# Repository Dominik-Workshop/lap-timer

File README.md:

# Lap Timer

## Overview

Compact and portable **lap timer**, capable of measuring time on:

- **Closed-loop tracks** (1-gate mode)
- **Start/finish tracks** (2-gate mode)

Infrared light barriers are used as optical triggers to detect when an object crosses the start or finish line.

### Key Features

- **High accuracy** using STM32 hardware timers
- **OLED display** for showing lap times
- **Two operating modes:** 1-gate or 2-gate
- **Modulated IR system (38 kHz)** for ambient light immunity

## Project Status

**Design:** ✅ --> **Fabrication & Assembly:** ✅ --> **Bring-up:** ✅

## Electronics

Simplified arhitecture of the **Lap Timer** is shown on the block diagram bellow:

This project contains 3 custom PCBs:

- [**Timer board**](/pcb/timer-board/): main PCB of the system, responsible for time measurement and displaying results

<!--  -->

- [**Transmitter board**](/pcb/transmitter-board/): generates the modulated IR light beam for the optical barrier

<!--  -->

- [**Receiver board**](/pcb/receiver-board/): (used only in 2-gate mode) detects the IR signal and triggers the timer

<!--  -->

## Mechanical

Each board has a custom-designed **3D printed enclosure**.

## Used Tools

- [KiCad](https://www.kicad.org/) - Schematic and PCB design
- [Autodesk Fusion 360](https://www.autodesk.com/products/fusion-360/) - 3D modeling
- [STM32CubeIDE](https://www.st.com/en/development-tools/stm32cubeide.html) - STM32 firmware development (build/flash/debug)

## Authors

- [**Dominik Pluta**](https://github.com/Dominik-Workshop):
  - **Responsibility**: [**Timer board**](/pcb/timer-board/)
- [**Mateusz Gwioździk**](https://github.com/Nojilim):
  - **Responsibility**: [**Transmitter board**](/pcb/transmitter-board/)
- [**Radek Mierzwa**](https://github.com/Radek278):
  - **Responsibility**: [**Receiver board**](/pcb/receiver-board/)

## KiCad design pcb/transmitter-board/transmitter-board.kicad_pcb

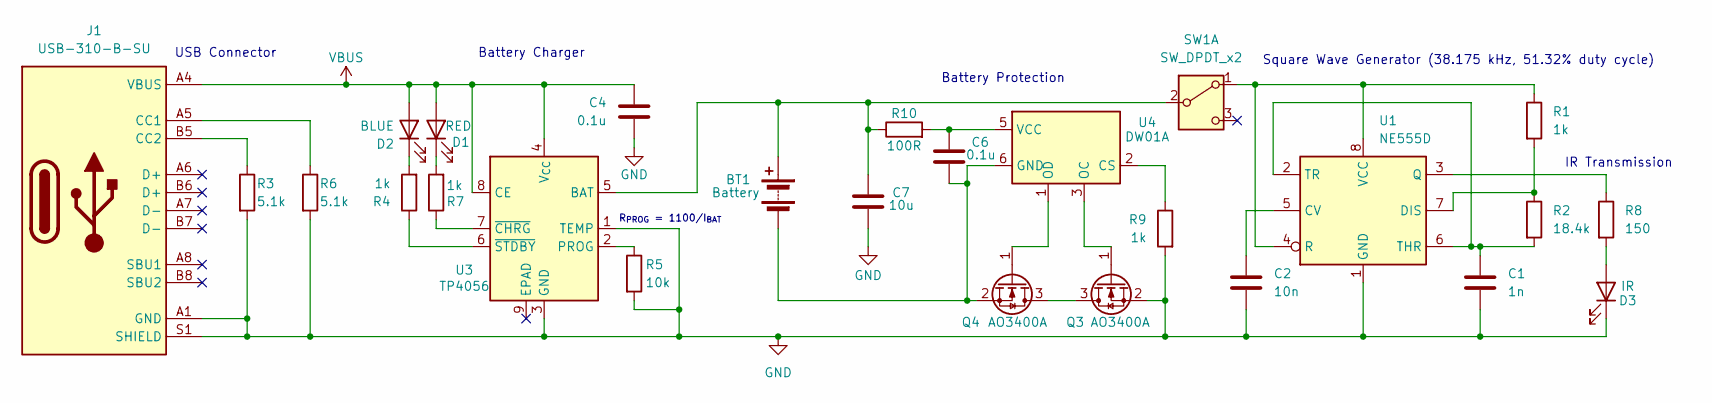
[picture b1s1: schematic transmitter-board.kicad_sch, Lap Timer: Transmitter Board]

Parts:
BT1: Battery; PinSocket_1x02_P2.54mm_Vertical
C1: 1n; C_0603_1608Metric_Pad1.08x0.95mm_HandSolder
C2: 10n; C_0603_1608Metric_Pad1.08x0.95mm_HandSolder
C4, C6: 0.1u; C_0603_1608Metric_Pad1.08x0.95mm_HandSolder
C7: 10u; C_0603_1608Metric_Pad1.08x0.95mm_HandSolder
D1: RED; LED_0603_1608Metric_Pad1.05x0.95mm_HandSolder
D2: BLUE; LED_0603_1608Metric_Pad1.05x0.95mm_HandSolder
D3: IR; LED_THT_Horizontal_SMD_mounted
J1: USB-C_USB-310F-B-SU; USB-C-Receptacle_USB-310-B-SU; MPN USB-310-B-SU; LCSC C309347
Q3, Q4: AO3400A; SOT-23
R1, R4, R7, R9: 1k; R_0603_1608Metric_Pad0.98x0.95mm_HandSolder
R2: 18.4k; R_0603_1608Metric_Pad0.98x0.95mm_HandSolder
R3, R6: 5.1k; R_0603_1608Metric_Pad0.98x0.95mm_HandSolder
R5: 10k; R_0603_1608Metric_Pad0.98x0.95mm_HandSolder
R8: 150; R_0603_1608Metric_Pad0.98x0.95mm_HandSolder
R10: 100R; R_0603_1608Metric_Pad0.98x0.95mm_HandSolder
SW1: SW_DPDT_x2; SW_DPDT_CK_JS202011JCQN
U1: NE555D; SOIC-8_3.9x4.9mm_P1.27mm
U3: TP4056; SOIC-8-1EP_3.9x4.9mm_P1.27mm_EP2.41x3.3mm_ThermalVias
U4: DW01A; SOT-23-6

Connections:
GND: C1.2, C2.2, C4.2, C7.2, D3.1 (K), J1.A1 (GND), J1.A12 (GND), J1.B1 (GND), J1.B12 (GND), J1.S1 (SHIELD), Q3.2 (S), R3.2, R5.2, R6.2, R9.2, U1.1 (GND), U3.1 (TEMP), U3.3 (GND)
unnamed: BT1.1 (+), C7.1, R10.1, SW1.2 (B), U3.5 (BAT)
unnamed: BT1.2 (-), C6.2, Q4.2 (S), U4.6 (GND)
unnamed: D1.1 (K), R7.2
unnamed: D2.1 (K), R4.2
unnamed: D3.2 (A), R8.2
unnamed: J1.A5 (CC1), R6.1
unnamed: J1.B5 (CC2), R3.1
unnamed: Q3.3 (D), Q4.3 (D)
unnamed: Q3.1 (G), U4.3 (OC)
unnamed: Q4.1 (G), U4.1 (OD)
unnamed: R1.1, SW1.1 (A), U1.4 (R), U1.8 (VCC)
unnamed: C2.1, U1.5 (CV)
unnamed: R1.2, R2.1, U1.7 (DIS)
unnamed: R8.1, U1.3 (Q)
unnamed: C1.1, R2.2, U1.2 (TR), U1.6 (THR)
unnamed: R5.1, U3.2 (PROG)
unnamed: R7.1, U3.7 (~CHRG)
unnamed: R4.1, U3.6 (~STDBY)
unnamed: R9.1, U4.2 (CS)
unnamed: C6.1, R10.2, U4.5 (VCC)
VBUS: C4.1, D1.2 (A), D2.2 (A), J1.A4 (VBUS), J1.A9 (VBUS), J1.B4 (VBUS), J1.B9 (VBUS), U3.4 (V_{CC}), U3.8 (CE)

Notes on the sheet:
IR Transmission
R_{PROG} = 1100/I_{BAT}
Battery Protection
USB Connector
Battery Charger
Square Wave Generator (38.175 kHz, 51.32% duty cycle)

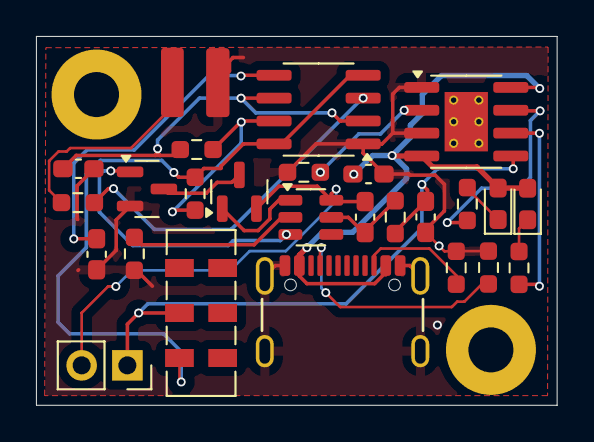
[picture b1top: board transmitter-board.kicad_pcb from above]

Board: 2 copper layers, 28.9 x 20.5 mm, 26 parts (0 on the bottom side), 22 nets.

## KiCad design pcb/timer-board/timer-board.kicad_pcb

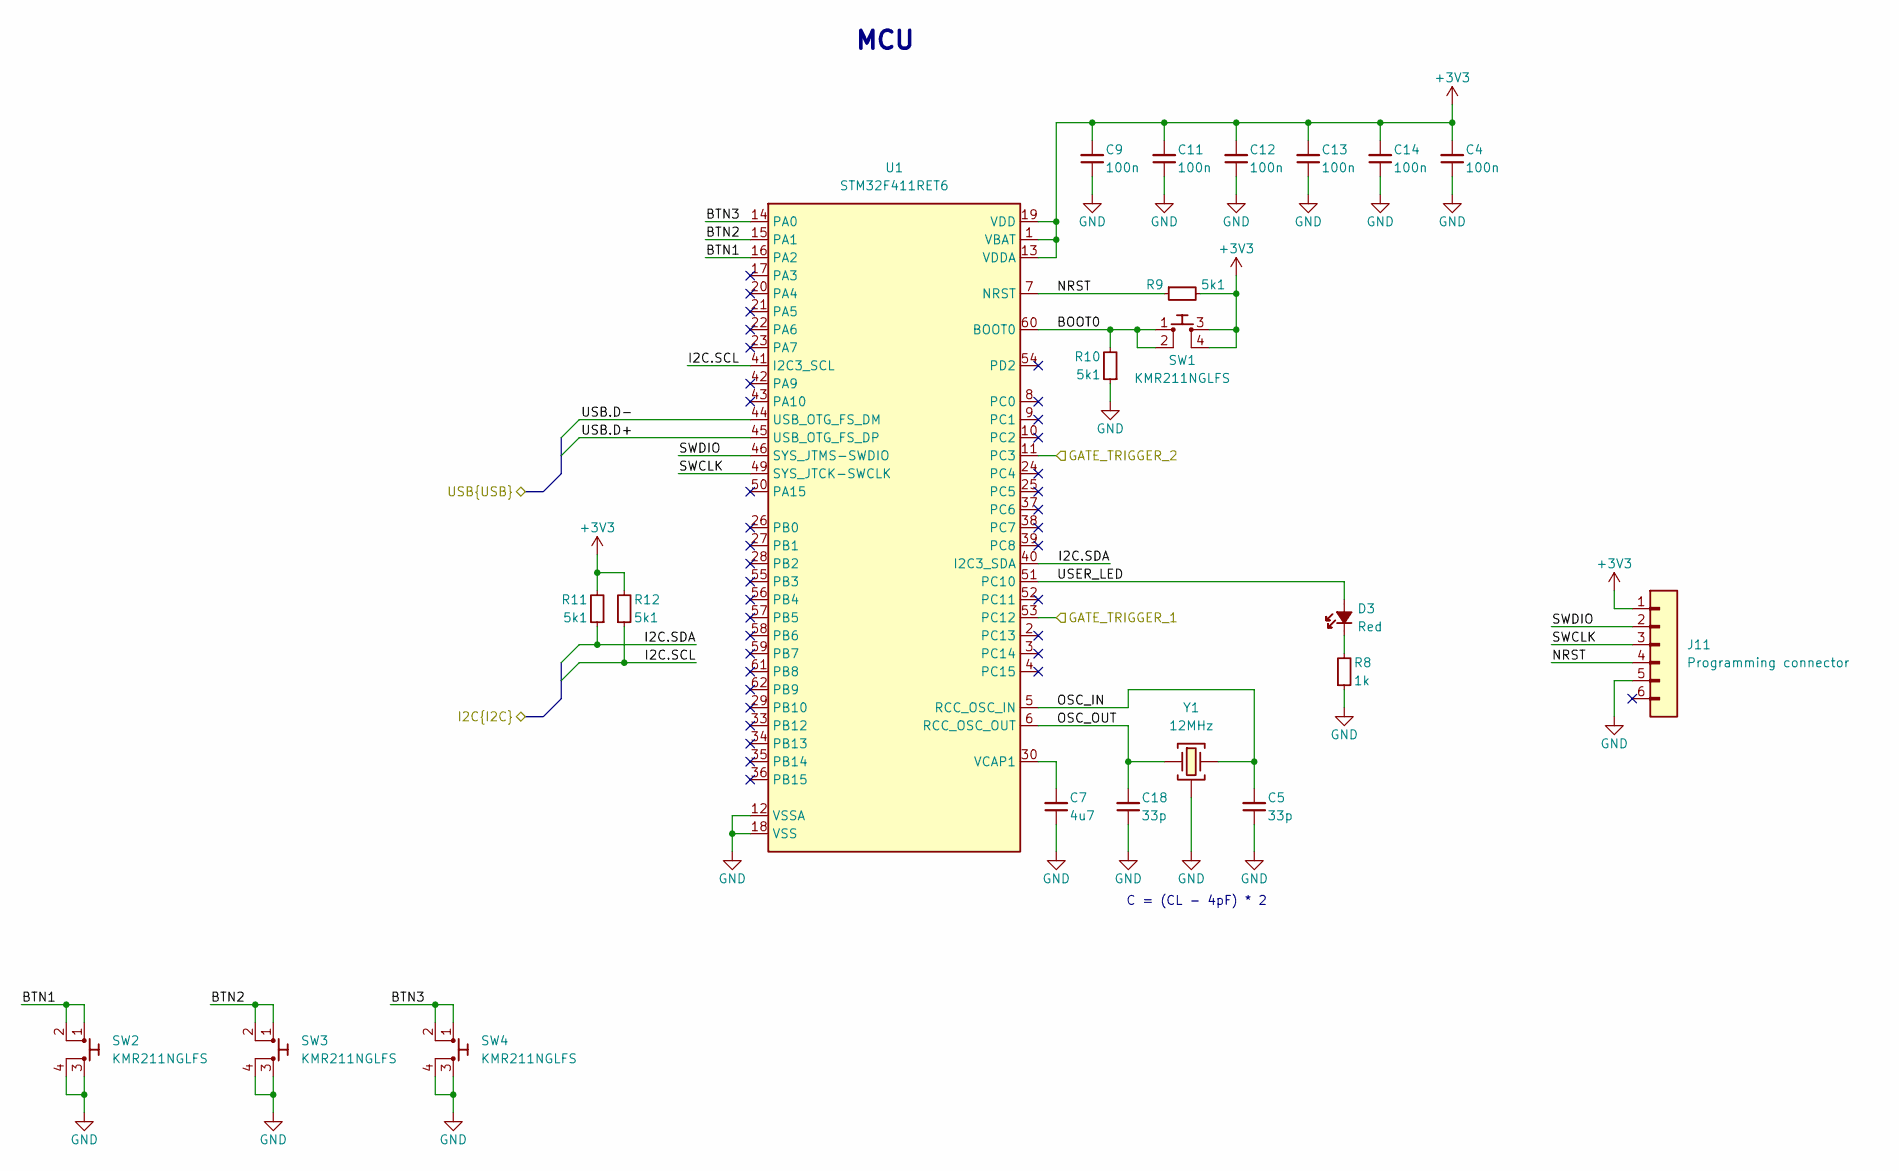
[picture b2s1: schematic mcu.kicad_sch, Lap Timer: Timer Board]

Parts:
C4, C9, C11, C12, C13, C14: C-100n-0402; C_0402_1005Metric; Tolerance 10%; Voltage 50V; MPN CL05B104KB54PNC; LCSC C307331
C5, C18: C-33p-0402; C_0402_1005Metric; Tolerance 5%; Voltage 50V; MPN 0402CG330J500NT; LCSC C1562
C7: C-4u7-0402; C_0402_1005Metric; Tolerance 20%; Voltage 10V; MPN CL05A475MP5NRNC; LCSC C23733
D3: LED-R-0603_KT-0603R; LED_0603_1608Metric_R; Forward voltage 1.8V-2.4V; MPN KT-0603R; LCSC C2286
J11: Programming connector; Custom-programming-connector-1x6_P1.27mm
R8: R-1k-0402; R_0402_1005Metric; Tolerance 1%; MPN 0402WGF1001TCE; LCSC C11702
R9, R10, R11, R12: R-5k1-0402; R_0402_1005Metric; Tolerance 1%; MPN 0402WGF5101TCE; LCSC C25905
SW1, SW2, SW3, SW4: SW_KMR211NGLFS; MPN KMR211NGLFS; LCSC C221676
U1: STM32F411RET6; LQFP-64_10x10mm_P0.5mm; MPN STM32F411RET6; LCSC C94355
Y1: X322512MSB4SI; Crystal_SMD_3225-4Pin_3.2x2.5mm; Frequency Tolerance ±10ppm; MPN X322512MSB4SI; LCSC C9002

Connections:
+3V3: C4.2, C9.2, C11.2, C12.2, C13.2, C14.2, J11.1, R9.2, R11.2, R12.2, SW1.3, SW1.4, U1.1 (VBAT), U1.13 (VDDA), U1.19 (VDD), U1.32 (VDD), U1.48 (VDD), U1.64 (VDD); also elsewhere on the board
/Display/I2C.SCL: R12.1, U1.41 (I2C3_SCL); also elsewhere on the board
/Display/I2C.SDA: R11.1, U1.40 (I2C3_SDA); also elsewhere on the board
/IR receiver/GATE_TRIGGER_1: U1.53 (PC12); also elsewhere on the board
/IR receiver/GATE_TRIGGER_2: U1.11 (PC3); also elsewhere on the board
/MCU/BOOT0: R10.2, SW1.1, SW1.2, U1.60 (BOOT0)
/MCU/BTN1: SW2.1, SW2.2, U1.16 (PA2)
/MCU/BTN2: SW3.1, SW3.2, U1.15 (PA1)
/MCU/BTN3: SW4.1, SW4.2, U1.14 (PA0)
/MCU/NRST: J11.4, R9.1, U1.7 (NRST)
/MCU/OSC_IN: C5.2, U1.5 (RCC_OSC_IN), Y1.3
/MCU/OSC_OUT: C18.2, U1.6 (RCC_OSC_OUT), Y1.1
/MCU/SWCLK: J11.3, U1.49 (SYS_JTCK-SWCLK)
/MCU/SWDIO: J11.2, U1.46 (SYS_JTMS-SWDIO)
/MCU/USB.D+: U1.45 (USB_OTG_FS_DP); also elsewhere on the board
/MCU/USB.D-: U1.44 (USB_OTG_FS_DM); also elsewhere on the board
/MCU/USER_LED: D3.2 (A), U1.51 (PC10)
GND: C4.1, C5.1, C7.1, C9.1, C11.1, C12.1, C13.1, C14.1, C18.1, J11.5, R8.1, R10.1, SW2.3, SW2.4, SW3.3, SW3.4, SW4.3, SW4.4, U1.12 (VSSA), U1.18 (VSS), U1.31 (VSS), U1.47 (VSS), U1.63 (VSS), Y1.2 (SH), Y1.4 (SH); also elsewhere on the board
unnamed: D3.1 (C), R8.2
unnamed: C7.2, U1.30 (VCAP1)

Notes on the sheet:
C = (CL - 4pF) * 2
MCU

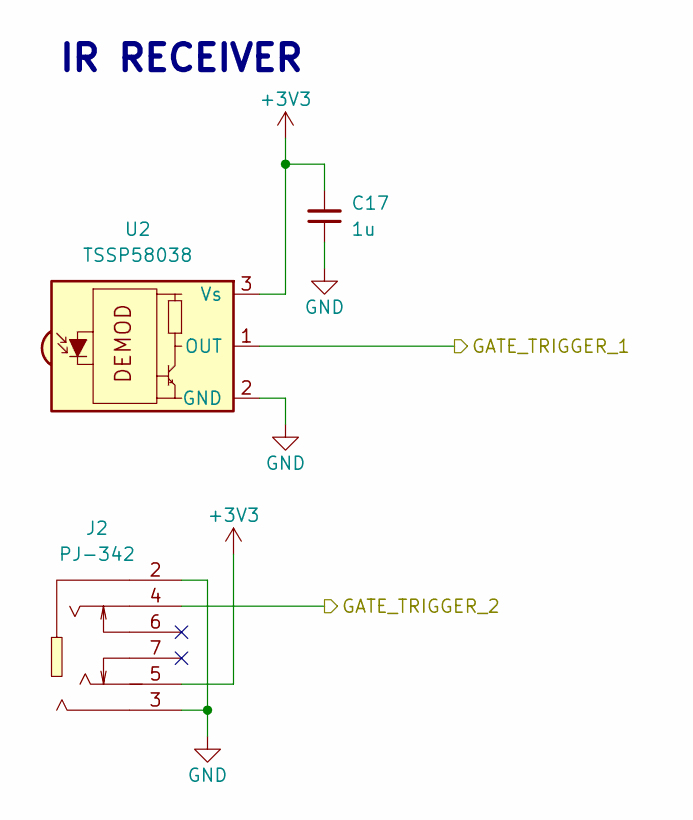
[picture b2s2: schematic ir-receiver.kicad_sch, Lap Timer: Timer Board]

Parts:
C17: C-1u-0402; C_0402_1005Metric; Tolerance 10%; Voltage 25V; MPN CL05A105KA5NQNC; LCSC C52923
J2: Jack_PJ-342; MPN PJ-342; LCSC C668606
U2: TSSP58038; Vishay_MINICAST-3Pin

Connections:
+3V3: C17.2, J2.5, U2.3 (Vs); also elsewhere on the board
/IR receiver/GATE_TRIGGER_1: U2.1 (OUT); also elsewhere on the board
/IR receiver/GATE_TRIGGER_2: J2.4; also elsewhere on the board
GND: C17.1, J2.2, J2.3, U2.2 (GND); also elsewhere on the board

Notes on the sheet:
IR RECEIVER

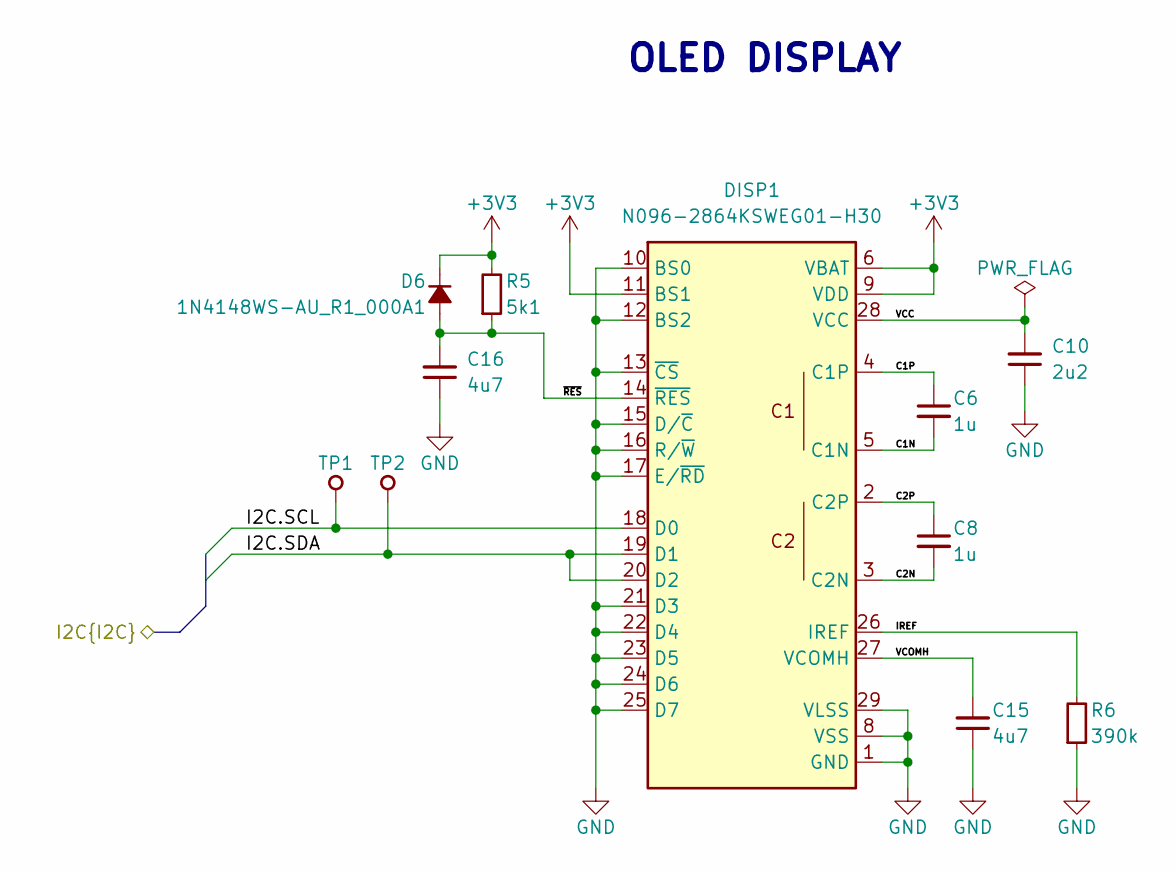
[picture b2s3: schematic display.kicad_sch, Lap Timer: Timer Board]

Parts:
C6, C8: C-1u-0402; C_0402_1005Metric; Tolerance 10%; Voltage 25V; MPN CL05A105KA5NQNC; LCSC C52923
C10: C-2u2-0402; C_0402_1005Metric; Tolerance 20%; Voltage 6.3V; MPN CL05A225MQ5NSNC; LCSC C12530
C15, C16: C-4u7-0402; C_0402_1005Metric; Tolerance 20%; Voltage 10V; MPN CL05A475MP5NRNC; LCSC C23733
D6: 1N4148WS-AU; D_SOD-323F; Reverse Voltage 75V; MPN 1N4148WS-AU_R1_000A1; LCSC C2999083
DISP1: N096-2864KSWEG01-H30; MPN N096-2864KSWEG01-H30
R5: R-5k1-0402; R_0402_1005Metric; Tolerance 1%; MPN 0402WGF5101TCE; LCSC C25905
R6: R-390k-0402; R_0402_1005Metric; Tolerance 1%; MPN 0402WGF3903TCE; LCSC C25782
TP1, TP2: TP_SMD_1mm

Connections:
+3V3: D6.1 (C), DISP1.6 (VBAT), DISP1.9 (VDD), DISP1.11 (BS1), R5.2; also elsewhere on the board
/Display/C1N: C6.2, DISP1.5 (C1N)
/Display/C1P: C6.1, DISP1.4 (C1P)
/Display/C2N: C8.2, DISP1.3 (C2N)
/Display/C2P: C8.1, DISP1.2 (C2P)
/Display/I2C.SCL: DISP1.18 (D0), TP1.1; also elsewhere on the board
/Display/I2C.SDA: DISP1.19 (D1), DISP1.20 (D2), TP2.1; also elsewhere on the board
/Display/IREF: DISP1.26 (IREF), R6.2
/Display/VCC: C10.2, DISP1.28 (VCC)
/Display/VCOMH: C15.2, DISP1.27 (VCOMH)
/Display/~RES: C16.2, D6.2 (A), DISP1.14 (~RES), R5.1
GND: C10.1, C15.1, C16.1, DISP1.1 (GND), DISP1.8 (VSS), DISP1.10 (BS0), DISP1.12 (BS2), DISP1.13 (~CS), DISP1.15 (D/~C), DISP1.16 (R/~W), DISP1.17 (E/~RD), DISP1.21 (D3), DISP1.22 (D4), DISP1.23 (D5), DISP1.24 (D6), DISP1.25 (D7), DISP1.29 (VLSS), DISP1.30 (GND), R6.1; also elsewhere on the board

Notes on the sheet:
OLED DISPLAY

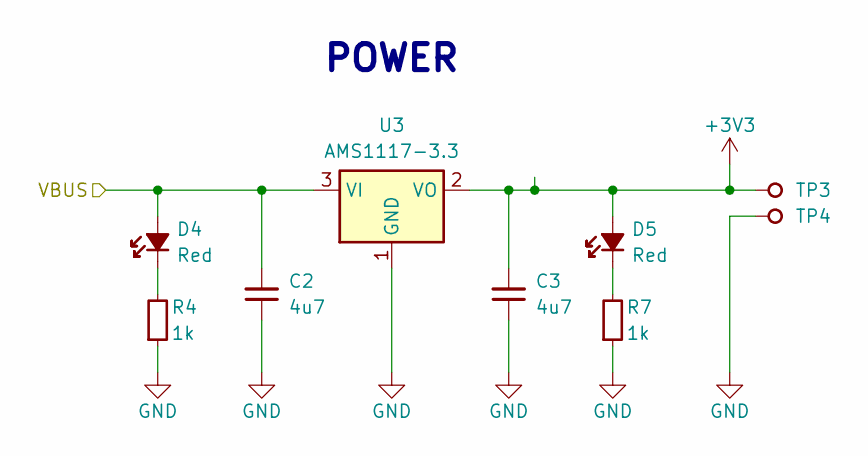
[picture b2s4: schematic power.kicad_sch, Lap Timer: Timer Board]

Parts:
C2, C3: C-4u7-0402; C_0402_1005Metric; Tolerance 20%; Voltage 10V; MPN CL05A475MP5NRNC; LCSC C23733
D4, D5: LED-R-0603_KT-0603R; LED_0603_1608Metric_R; Forward voltage 1.8V-2.4V; MPN KT-0603R; LCSC C2286
R4, R7: R-1k-0402; R_0402_1005Metric; Tolerance 1%; MPN 0402WGF1001TCE; LCSC C11702
TP3, TP4: TP_SMD_1mm
U3: AMS1117-3.3; SOT-223-3_TabPin2

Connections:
+3V3: C3.2, D5.2 (A), TP3.1, U3.2 (VO); also elsewhere on the board
/Power/VBUS: C2.2, D4.2 (A), U3.3 (VI); also elsewhere on the board
GND: C2.1, C3.1, R4.1, R7.1, TP4.1, U3.1 (GND); also elsewhere on the board
unnamed: D4.1 (C), R4.2
unnamed: D5.1 (C), R7.2

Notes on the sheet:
POWER

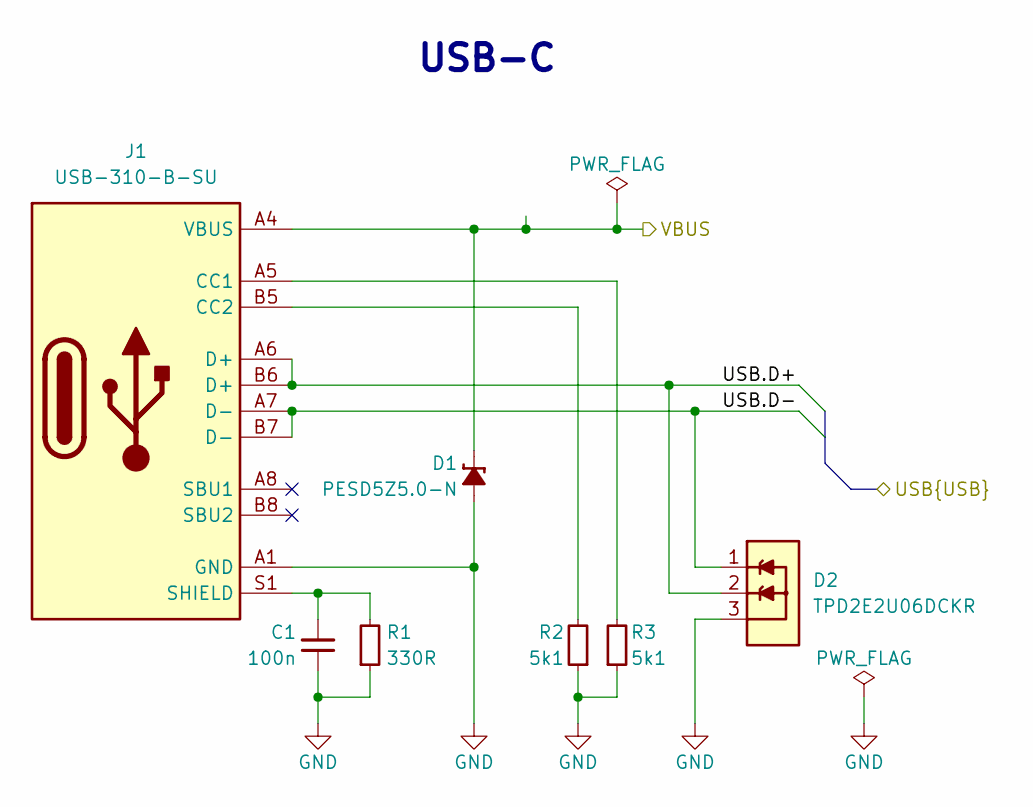
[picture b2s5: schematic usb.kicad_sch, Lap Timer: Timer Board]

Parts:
C1: C-100n-0402; C_0402_1005Metric; Tolerance 10%; Voltage 50V; MPN CL05B104KB54PNC; LCSC C307331
D1: PESD5Z5; D_SOD-523; MPN PESD5Z5.0-N; LCSC C920301
D2: TPD2E2U06DCKR; SOT-323; MPN TPD2E2U06DCKR; LCSC C1855726
J1: USB-C_USB-310F-B-SU; USB-C-Receptacle_USB-310-B-SU; MPN USB-310-B-SU; LCSC C309347
R1: R-330r-0402; R_0402_1005Metric; Tolerance 1%; MPN 0402WGF3300TCE; LCSC C25104
R2, R3: R-5k1-0402; R_0402_1005Metric; Tolerance 1%; MPN 0402WGF5101TCE; LCSC C25905

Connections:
/MCU/USB.D+: D2.2, J1.A6 (D+), J1.B6 (D+); also elsewhere on the board
/MCU/USB.D-: D2.1, J1.A7 (D-), J1.B7 (D-); also elsewhere on the board
/Power/VBUS: D1.1 (C), J1.A4 (VBUS), J1.A9 (VBUS), J1.B4 (VBUS), J1.B9 (VBUS); also elsewhere on the board
GND: C1.1, D1.2 (A), D2.3, J1.A1 (GND), J1.A12 (GND), J1.B1 (GND), J1.B12 (GND), R1.1, R2.1, R3.1; also elsewhere on the board
unnamed: J1.A5 (CC1), R3.2
unnamed: J1.B5 (CC2), R2.2
unnamed: C1.2, J1.S1 (SHIELD), R1.2

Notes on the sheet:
USB-C

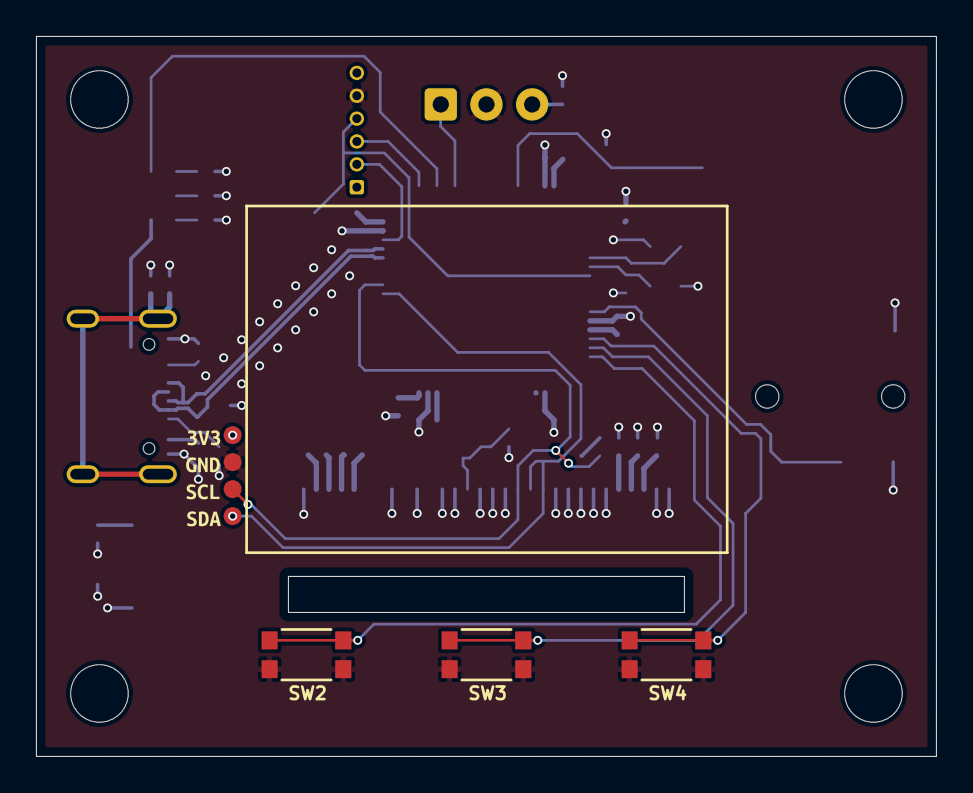
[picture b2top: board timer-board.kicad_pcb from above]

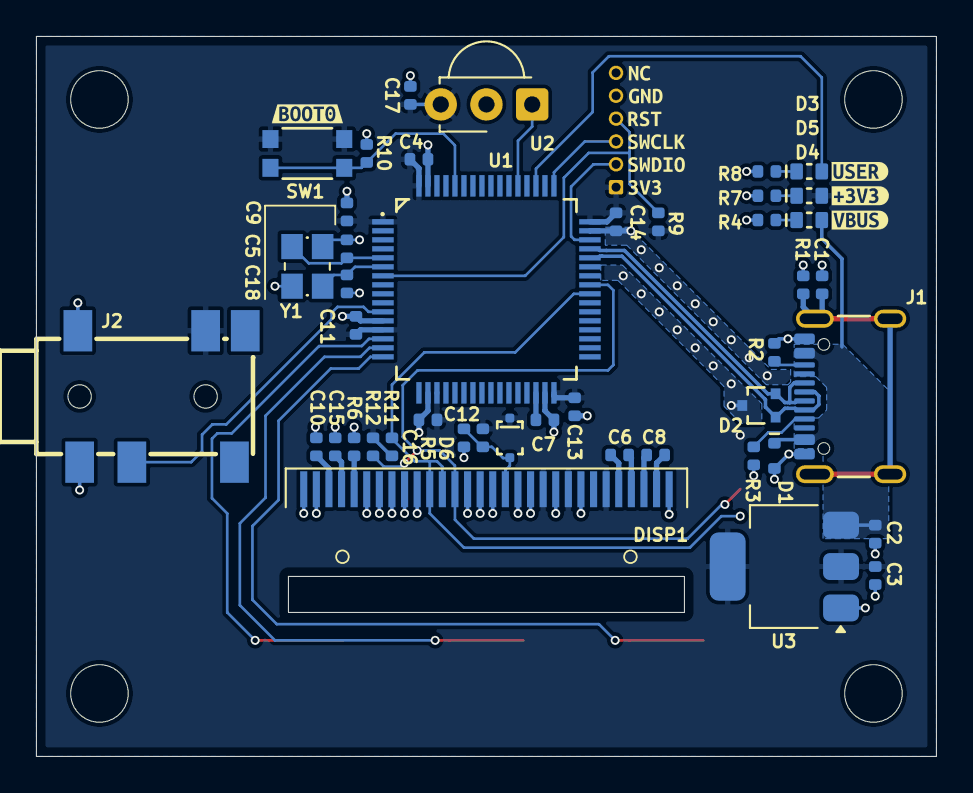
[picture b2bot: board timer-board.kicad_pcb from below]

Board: 2 copper layers, 50.0 x 40.0 mm, 66 parts (55 on the bottom side), 34 nets.

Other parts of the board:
kibuzzard-68E6B0E6: G***; kibuzzard-68E6B0E6
kibuzzard-68E6B17C: G***; kibuzzard-68E6B17C
kibuzzard-68E6B138: G***; kibuzzard-68E6B138
kibuzzard-68E6B152: G***; kibuzzard-68E6B152
kibuzzard-68E6B182: G***; kibuzzard-68E6B182
kibuzzard-68FD2D82: G***; kibuzzard-68FD2D82
kibuzzard-690B1D8E: G***; kibuzzard-690B1D8E
kibuzzard-690B1DCB: G***; kibuzzard-690B1DCB
kibuzzard-690B1DD3: G***; kibuzzard-690B1DD3
kibuzzard-690B1DD8: G***; kibuzzard-690B1DD8
kibuzzard-690B8D6F: G***; kibuzzard-690B8D6F
kibuzzard-691094F6: G***; kibuzzard-691094F6
kibuzzard-69109507: G***; kibuzzard-69109507
kibuzzard-69109536: G***; kibuzzard-69109536

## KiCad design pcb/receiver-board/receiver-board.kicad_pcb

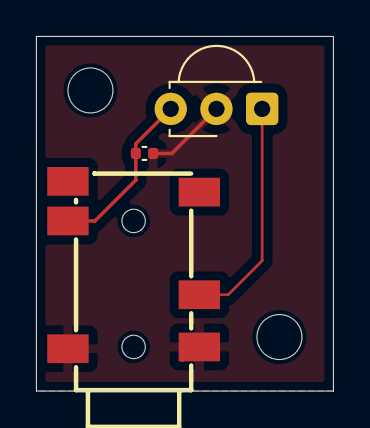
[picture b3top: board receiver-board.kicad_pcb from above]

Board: 2 copper layers, 16.5 x 19.7 mm, 3 parts (0 on the bottom side), 3 nets.

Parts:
C6: C-1u-0402; C_0402_1005Metric
J2: Jack_PJ-342
U2: TSSP58038; Vishay_MINICAST-3Pin

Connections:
+3V3: C6.1, J2.5, U2.3 (Vs)
/GATE_TRIGGER2: J2.4, U2.1 (OUT)
GND: C6.2, J2.2, J2.3, U2.2 (GND)

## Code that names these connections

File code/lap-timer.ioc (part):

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Mcu.Name=STM32F411R(C-E)Tx
Mcu.Package=LQFP64
Mcu.UserName=STM32F411RETx
PA0-WKUP.GPIOParameters=GPIO_PuPd,GPIO_Label
PA0-WKUP.GPIO_Label=BTN3
PA0-WKUP.GPIO_PuPd=GPIO_PULLUP
PA0-WKUP.Signal=GPIO_Input
PA1.GPIOParameters=GPIO_PuPd,GPIO_Label
PA1.GPIO_Label=BTN2
PA1.GPIO_PuPd=GPIO_PULLUP
PA1.Signal=GPIO_Input
PA2.GPIOParameters=GPIO_PuPd,GPIO_Label
PA2.GPIO_Label=BTN1
PA2.GPIO_PuPd=GPIO_PULLUP
PA2.Signal=GPXTI2
PA8.Mode=I2C
PA8.Signal=I2C3_SCL
PC10.GPIOParameters=GPIO_Label
PC10.GPIO_Label=USER_LED
PC10.Signal=GPIO_Output
PC12.GPIOParameters=GPIO_PuPd,GPIO_Label,GPIO_ModeDefaultEXTI
PC12.GPIO_Label=GATE_TRIGGER_1
PC12.GPIO_ModeDefaultEXTI=GPIO_MODE_IT_RISING
PC12.GPIO_PuPd=GPIO_PULLUP
PC12.Signal=GPXTI12
PC3.GPIOParameters=GPIO_PuPd,GPIO_Label
PC3.GPIO_Label=GATE_TRIGGER_2
PC3.GPIO_PuPd=GPIO_PULLUP
PC3.Signal=GPXTI3
PC9.Mode=I2C
PC9.Signal=I2C3_SDA
PH0\ -\ OSC_IN.Mode=HSE-External-Oscillator
PH0\ -\ OSC_IN.Signal=RCC_OSC_IN
PH1\ -\ OSC_OUT.Mode=HSE-External-Oscillator
PH1\ -\ OSC_OUT.Signal=RCC_OSC_OUT
RCC.HSE_VALUE=12000000
RCC.SYSCLKFreq_VALUE=100000000
RCC.SYSCLKSource=RCC_SYSCLKSOURCE_PLLCLK
board=custom

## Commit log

2025-10-19 Initialize KiCad projects, setup design rules, pre-defined sizes and net classes
2025-10-19 [#1] Draft project assumptions
2025-10-19 [#1] Improve block diagram
2025-10-19 Update README with project details
2025-10-19 [#1] Update project assumptions
2025-10-19 [#1] Add planed development schedule
2025-11-02 Add transmitter-board schematics
2025-11-02 Change package to 0603
2025-11-02 Add receiver-board schematic and pcb
2025-11-03 Add transmitter-board pcb
2025-11-04 Change hole size under TP4056 and change battery connector to THT.
2025-11-08 receiver-board
2025-11-08 Added capacitor and changed jack on receiver board
2025-11-08 replace whole on receiver board
2025-11-09 Clear DRC, move audio jack and resize the board, update title block author and date
2025-11-09 Remove production files
2025-11-09 Change USB and battery connector
2025-11-09 Move USB
2025-11-09 Change R5 value
2025-11-09 Start schematic design of the timer board, add MCU, USB, IR receiver and OLED
2025-11-09 Finish uncompleted schematic sections, layout most of the PCB
2025-11-09 Layout power planes and different signals
2025-11-09 Add 3.5mm jack, fix BOOT0 connection
2025-11-09 Connect OLED display, position main components
2025-11-09 Add I2C pull-up, IR receiver decoupling, LED labels, clear ERC and DRC
2025-11-09 Fix typo and add project authors section in README
2025-11-12 Initialize STM Cube IDE project
2025-12-21 Edited transmitter-board schematic
2025-12-21 Change schematic look
2025-12-21 Refactor transmitter-board schematic
2025-12-21 Final refactor transmitter-board schematic
2025-12-21 Clear ERC and DRC
2026-01-14 Add test blink code
2026-01-14 Test interrupt triggering with BTN1
2026-01-14 Test main sensor triggering
2026-01-14 Setup pin configuration with appropriate names
2026-01-14 WIP: Use pin interrupt
2026-01-14 Fix floating GATE_TRIGER_2 pin
2026-01-14 Remove unused sprites
2026-01-14 Add short/long reset button press functions, add additional timer trigger pins - BTN1 and GATE_TRIG_2
2026-01-14 Add desciptions for time sections
2026-01-14 Change trigger from falling to rising edge
2026-01-14 Test data displaying
2026-01-14 Test the OLED display
2026-01-14 Add sprite generator script, minor logo remake
2026-01-14 Add best time storage
2026-01-14 Display dummy time, increase I2C speed
2026-01-14 Add high resolution mode
2026-01-14 Add debouncing at stop, add reset button
2026-01-14 First working timer
2026-01-27 Update design status and used tools sections in README
2026-01-27 Add Timer Board enclosure 3D model
2026-01-27 Add description in main.c
2026-03-27 Add timer module photo to README
